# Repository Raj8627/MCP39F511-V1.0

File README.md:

# MCP39F511-V1.0
Power Monitoring Using MCP39F511 Eagle PCB Breakout

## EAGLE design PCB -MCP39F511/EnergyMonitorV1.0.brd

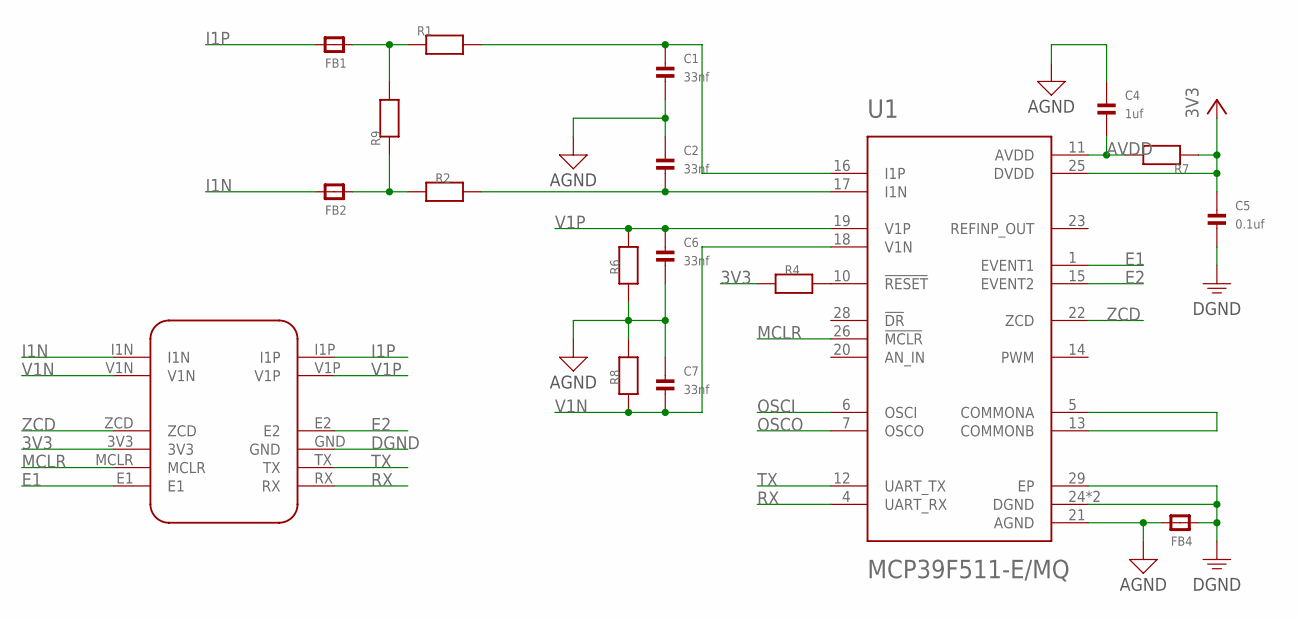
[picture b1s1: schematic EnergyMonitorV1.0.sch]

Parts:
C1, C2, C6, C7: 33nf; 0603
C4: 1uf; 0603
C5: 0.1uf; 0603
FB1, FB2, FB4: FERRITE_0603; _0603
R1, R2, R6, R8: 1k; 0603
R4, R7: 10R; 0603
R9: 2.49; 0603
U1: MCP39F511-E/MQ; QFN50P500X500X100-29N
U$1: PMIC

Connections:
3V3: C5.1, R4.1, R7.1, U1.25 (DVDD), U$1.3V3
AGND: C1.2, C2.1, C4.1, C6.2, C7.1, FB4.1, R6.1, R8.2, U1.21 (AGND)
AVDD: C4.2, R7.2, U1.11 (AVDD)
DGND: C5.2, FB4.2, U1.24 (DGND), U1.27 (DGND), U1.29 (EP), U$1.GND
E1: U1.1 (EVENT1), U$1.E1
E2: U1.15 (EVENT2), U$1.E2
I1N: FB2.1, U$1.I1N
I1P: FB1.1, U$1.I1P
MCLR: U1.26 (!MCLR), U$1.MCLR
unnamed: C1.1, R1.2, U1.16 (I1P)
unnamed: C2.2, R2.2, U1.17 (I1N)
unnamed: U1.5 (COMMONA), U1.13 (COMMONB)
unnamed: R4.2, U1.10 (!RESET)
unnamed: FB1.2, R1.1, R9.2
unnamed: FB2.2, R2.1, R9.1
OSCI: U1.6 (OSCI)
OSCO: U1.7 (OSCO)
RX: U1.4 (UART_RX), U$1.RX
TX: U1.12 (UART_TX), U$1.TX
V1N: C7.2, R8.1, U1.18 (V1N), U$1.V1N
V1P: C6.1, R6.2, U1.19 (V1P), U$1.V1P
ZCD: U1.22 (ZCD), U$1.ZCD

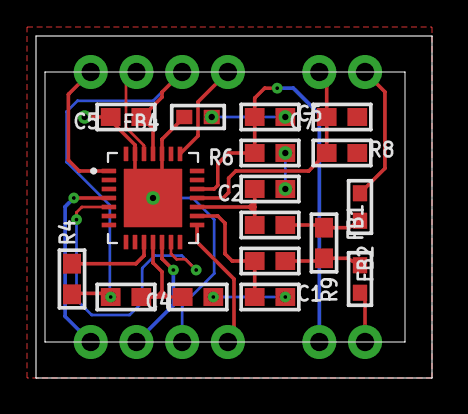
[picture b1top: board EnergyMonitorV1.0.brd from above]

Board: 2 copper layers, 22.0 x 19.0 mm, 18 parts (0 on the bottom side), 20 nets.

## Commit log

2020-08-15 eagle

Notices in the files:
parts and their libraries:
microbuilder: This work is placed in the public domain, and may be freely used for commercial and non-commercial work with the following conditions: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
